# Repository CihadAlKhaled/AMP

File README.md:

# Acceleration Monitor PCB (AMP)

## Background 
The AMP tracks acceleration in the x, y, and z-axis in units of Earth's gravitational acceleration (g). 

## Design
The PCB is powered via a USB connection, which supplies both power and data communication to the computer. An MPU6050 tracks acceleration, which is read by an RP2040 microcontroller over an I²C interface. The computer receives this data and displays it in a console. A 1x2 connector allows the AMP to enter **BOOTSEL** mode when shorted. Additionally, a crystal oscillator provides a stable clock signal for timing operations.

The AMP was designed using KiCad:

### Schematics Design

**Figure 1.0**  

### PCB Design

**Figure 1.1**  

### 3D Rendering of AMP

**Figure 1.2**  

## Hardware
All parts were bought and put together by [JLCPCB](https://jlcpcb.com/). **Table 2.0** has a list of all the components used in the AMP.  

**Table 2.0**  

## Physical PCB
The board arrived, and in **Figure 3.1**, the 1x2 connector is shorted using the red wire, thus in **BOOTSEL** mode.  

### AMP  

**Figure 3.0** 

### BOOTSEL Mode  
  
**Figure 3.1**  

## Software
The software was programmed in MicroPython and uploaded to the RP2040's file system. The software configures the I²C interface by initializing the RP2040's GPIO28 and GPIO29 to the SDA and SCL of the MPU6050. The MPU6050 has a standardized address that the RP2040 communicates with to wake it up and start collecting acceleration data from the AMP.  

### Code uploaded onto the AMP  
  
**Figure 4.0**  

### Output
The code displays the data from the AMP onto the console, showing the x, y, and z components of the acceleration in units of g.  

### Stationary

When the AMP is placed stationary and upright, the z component represents the Earth's gravity on the AMP (~1g = 9.8 m/s²), while x and y are close to zero g. Shown in **Figure 4.1**, there is a slight discrepancy due to the AMP not being perfectly upright, causing Earth's gravity to also appear in the x and y components. Additionally, some noise is present in the readings.  

**Figure 4.1**  

### AMP says WOOF!

The AMP was getting antsy staying stationary, so it went on a walk in the negative y direction while slowly increasing acceleration, as shown in **Figure 4.2**.  

**Figure 4.2**  

### AMP goes up, up, up... and back down?

The AMP being thrown into the air was mimicked (no broken PCB today!). The z-axis shows the acceleration of it going up and then coming back down, as shown in **Figure 4.3**.  

**Figure 4.3**  

### "Around we go"

The AMP was swung around in a circle, and the y-axis represents the measured centripetal acceleration of the PCB, as shown in **Figure 4.4**. The centripetal acceleration could be used to calculate the tension of the wire connecting the computer and the AMP.  

**Figure 4.4**  

## Challenges 
The AMP project was my first PCB design, making it a challenging but valuable learning experience. Understanding how each chip interacted with the others was challenging, and extracting relevant information from datasheets was a struggle in itself. Learning how to **read and interpret datasheets** is a skill I need to continue developing if I want to keep making PCBs.

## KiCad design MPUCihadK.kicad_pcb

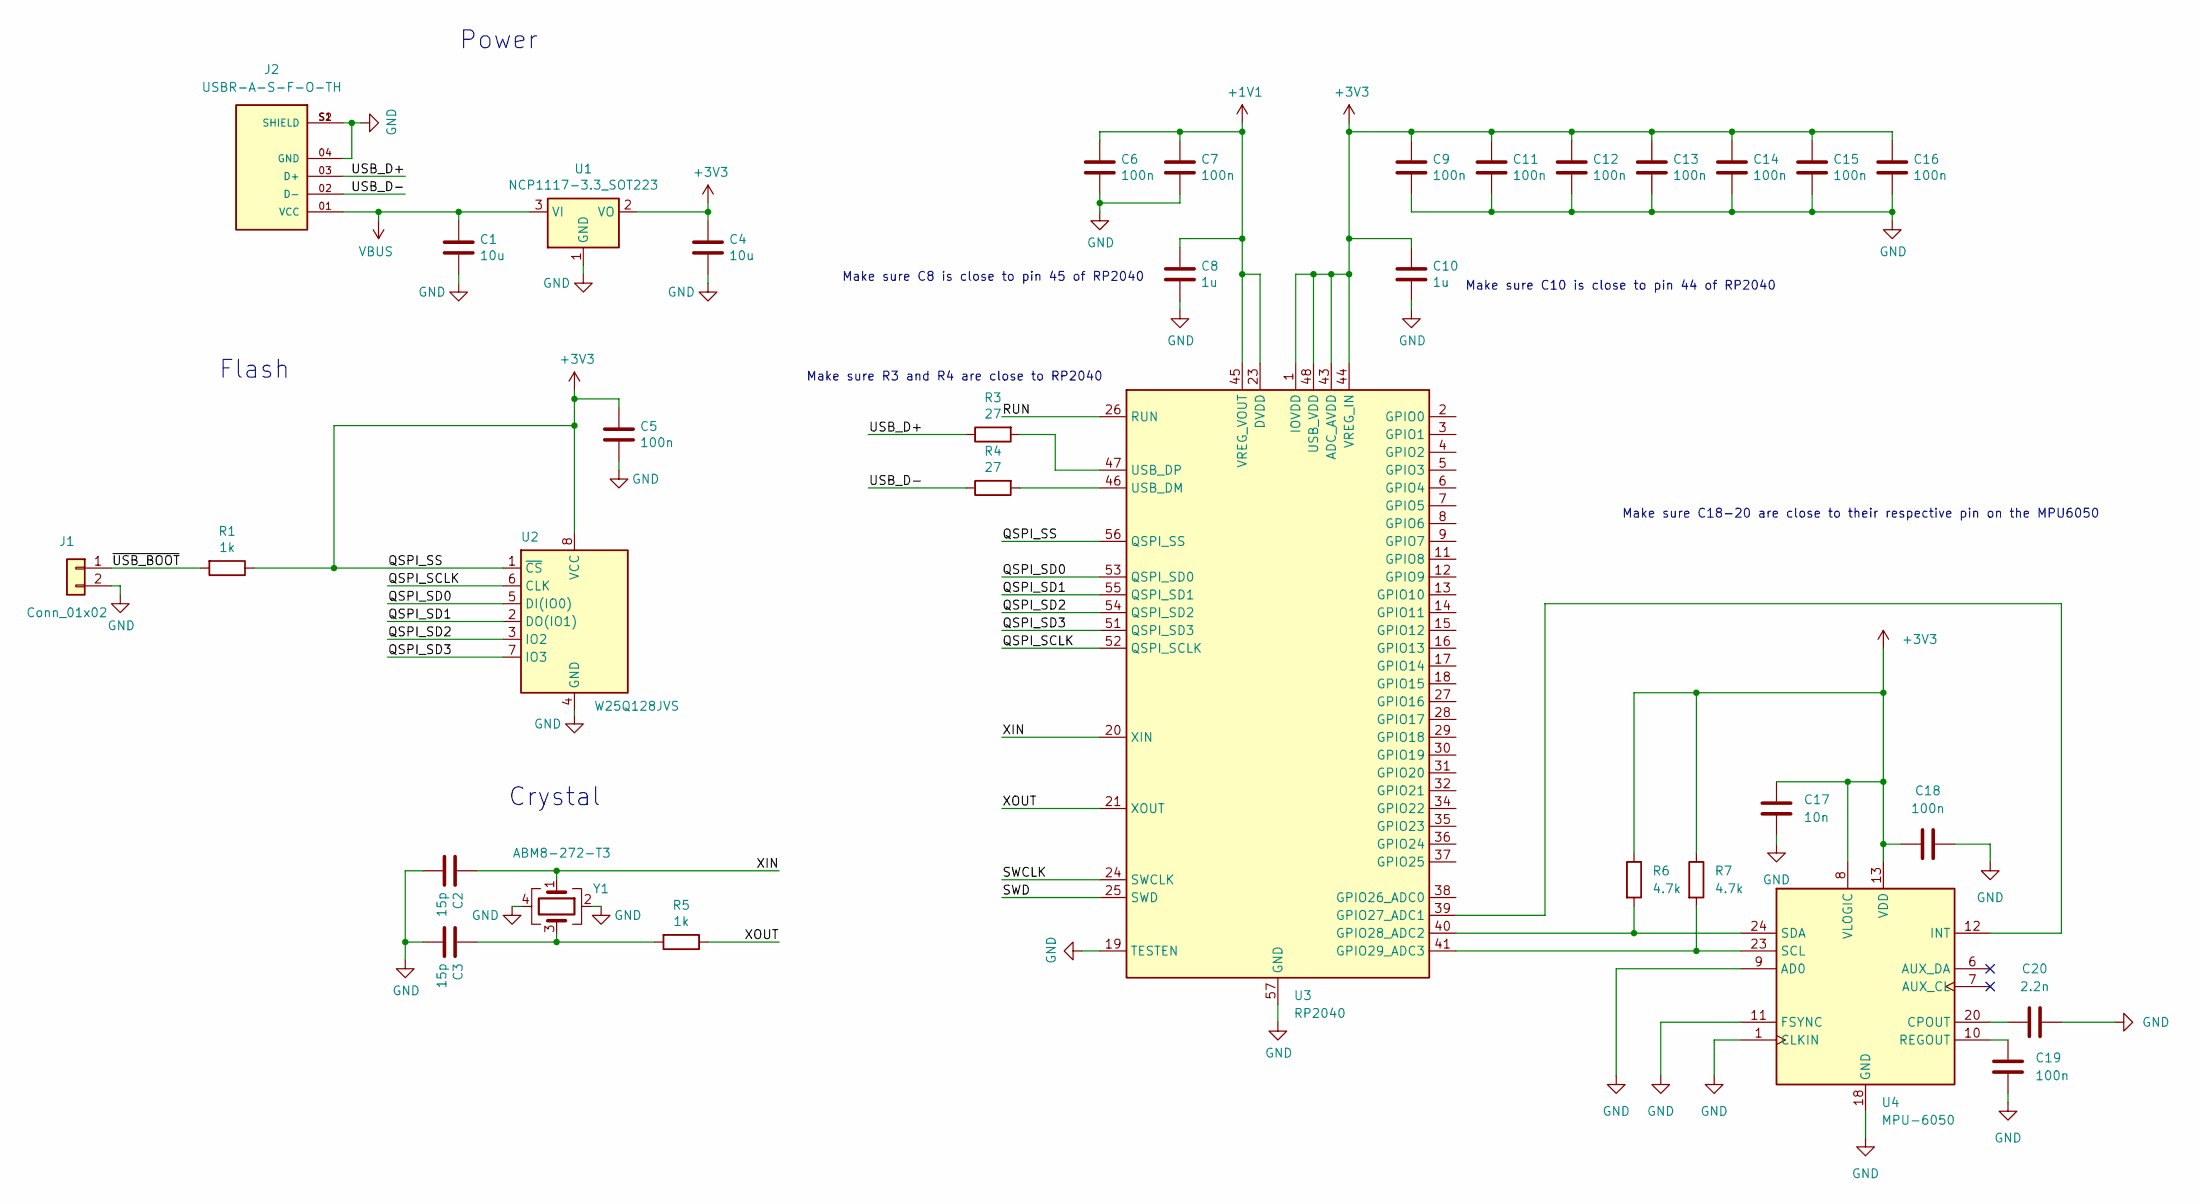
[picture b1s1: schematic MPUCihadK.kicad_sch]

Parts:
C1, C4: 10u; C_0805_2012Metric; LCSC C15525
C2, C3: 15p; C_0402_1005Metric; LCSC C32949
C5, C6, C7, C9, C11, C12, C13, C14, C15, C16, C18, C19: 100n; C_0402_1005Metric; LCSC C1525
C8, C10: 1u; C_0402_1005Metric; LCSC C52923
C17: 10n; C_0402_1005Metric; LCSC C15195
C20: 2.2n; C_0402_1005Metric; LCSC C1531
J1: Conn_01x02; PinHeader_1x02_P2.54mm_Vertical; LCSC C49661
J2: USBR-A-S-F-O-TH; SAMTEC_USBR-A-S-F-O-TH; PARTREV L; LCSC C3197891
R1, R5: 1k; R_0402_1005Metric; LCSC C25543
R3, R4: 27; R_0402_1005Metric; LCSC C25100
R6, R7: 4.7k; R_0402_1005Metric; LCSC C105871
U1: NCP1117-3.3_SOT223; SOT-223-3_TabPin2; LCSC C26537
U2: W25Q128JVS; SOIC-8_5.23x5.23mm_P1.27mm; LCSC C2613930
U3: RP2040; QFN-56-1EP_7x7mm_P0.4mm_EP3.2x3.2mm; LCSC C2040
U4: MPU-6050; InvenSense_QFN-24_4x4mm_P0.5mm; LCSC C24112
Y1: ABM8-272-T3; Crystal_SMD_3225-4Pin_3.2x2.5mm; LCSC C20625731

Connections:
+1V1: C6.1, C7.1, C8.1, U3.23 (DVDD), U3.45 (VREG_VOUT), U3.50 (DVDD)
/QSPI_SCLK: U2.6 (CLK), U3.52 (QSPI_SCLK)
/QSPI_SD0: U2.5 (DI(IO0)), U3.53 (QSPI_SD0)
/QSPI_SD1: U2.2 (DO(IO1)), U3.55 (QSPI_SD1)
/QSPI_SD2: U2.3 (IO2), U3.54 (QSPI_SD2)
/QSPI_SD3: U2.7 (IO3), U3.51 (QSPI_SD3)
/RUN: U3.26 (RUN)
/SWCLK: U3.24 (SWCLK)
/SWD: U3.25 (SWD)
/USB_D+: J2.03 (D+), R3.1
/USB_D-: J2.02 (D-), R4.1
/XIN: C2.1, U3.20 (XIN), Y1.1
/XOUT: R5.1, U3.21 (XOUT)
/~USB_BOOT: J1.1, R1.2
GND: C1.2, C2.2, C3.2, C4.2, C5.2, C6.2, C7.2, C8.2, C9.2, C10.2, C11.2, C12.2, C13.2, C14.2, C15.2, C16.2, C17.2, C18.2, C19.2, C20.2, J1.2, J2.04 (GND), J2.S1 (SHIELD), J2.S2 (SHIELD), U1.1 (GND), U2.4 (GND), U3.19 (TESTEN), U3.57 (GND), U4.1 (CLKIN), U4.9 (AD0), U4.11 (FSYNC), U4.18 (GND), Y1.2, Y1.4
unnamed: C3.1, R5.2, Y1.3
unnamed: U3.39 (GPIO27_ADC1), U4.12 (INT)
unnamed: R6.2, U3.40 (GPIO28_ADC2), U4.24 (SDA)
unnamed: R7.2, U3.41 (GPIO29_ADC3), U4.23 (SCL)
unnamed: R4.2, U3.46 (USB_DM)
unnamed: R3.2, U3.47 (USB_DP)
unnamed: C20.1, U4.20 (CPOUT)
unnamed: C19.1, U4.10 (REGOUT)
VBUS: C1.1, J2.01 (VCC), U1.3 (VI)

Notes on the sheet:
Make sure C8 is close to pin 45 of RP2040
Make sure C10 is close to pin 44 of RP2040
Make sure C18-20 are close to their respective pin on the MPU6050
Make sure R3 and R4 are close to RP2040
Crystal
Power
Flash

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
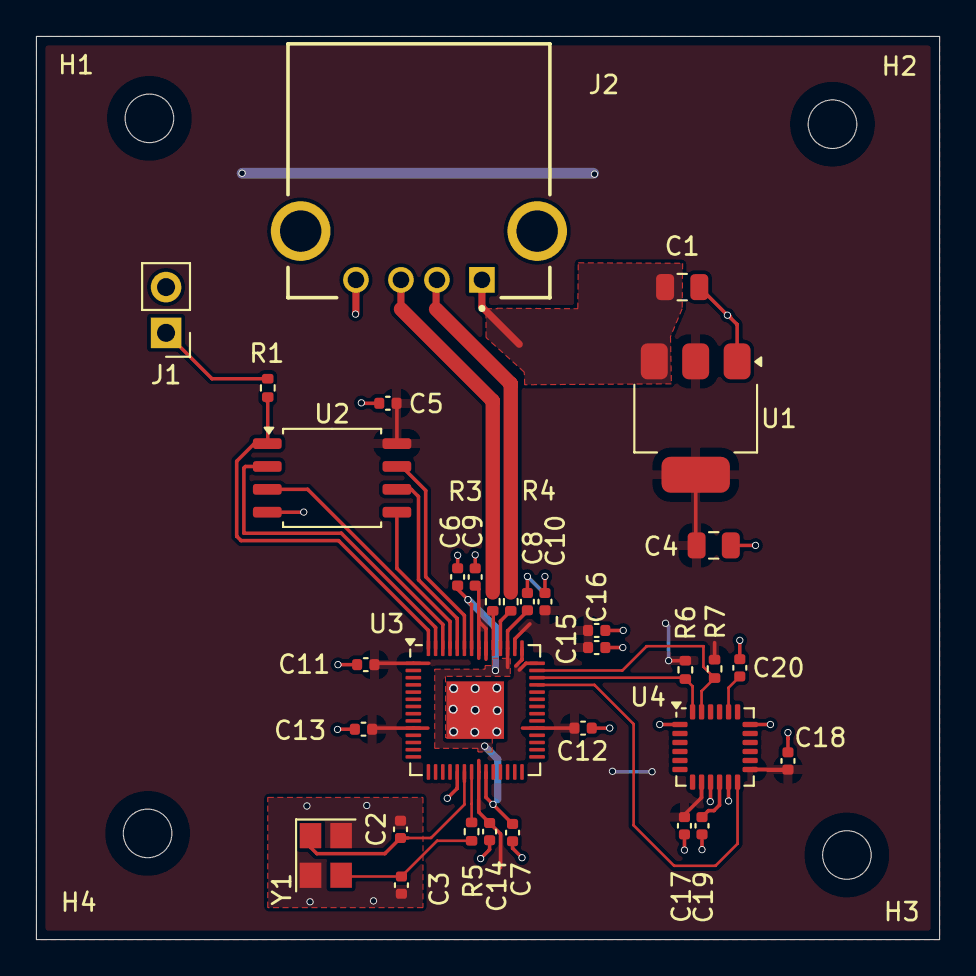
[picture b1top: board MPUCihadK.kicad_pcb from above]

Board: 2 copper layers, 50.2 x 50.2 mm, 37 parts (0 on the bottom side), 23 nets.

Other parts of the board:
H1, H2, H3, H4: MountingHole; MountingHole_2.7mm_M2.5

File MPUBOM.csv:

"Reference","Value","Datasheet","Footprint","Qty","DNP","LCSC","Link"
"C1,C4","10u","https://www.lcsc.com/datasheet/lcsc_datasheet_2208231630_Sam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","Capacitor_SMD:C_0805_2012Metric","2","","C15525","https://jlcpcb.com/partdetail/C15525"
"C2,C3","15p","https://www.lcsc.com/datasheet/lcsc_datasheet_2304140030_Sam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","Capacitor_SMD:C_0402_1005Metric","2","","C32949","https://jlcpcb.com/partdetail/C32949"
"C5,C6,C7,C9,C11,C12,C13,C14,C15,C16,C18,C19","100n","https://www.lcsc.com/datasheet/lcsc_datasheet_2304140030_Sam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","Capacitor_SMD:C_0402_1005Metric","12","","C1525","https://jlcpcb.com/partdetail/C1525"
"C8,C10","1u","https://www.lcsc.com/datasheet/lcsc_datasheet_2304140030_Sam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","Capacitor_SMD:C_0402_1005Metric","2","","C52923","https://jlcpcb.com/partdetail/C52923"
"C17","10n","https://www.lcsc.com/datasheet/lcsc_datasheet_2304140030_Sam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","Capacitor_SMD:C_0402_1005Metric","1","","C15195","https://jlcpcb.com/partdetail/15869-CL05B103KB5NNNC/C15195"
"C20","2.2n","https://www.lcsc.com/datasheet/lcsc_datasheet_2304140030_FH-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","Capacitor_SMD:C_0402_1005Metric","1","","C1531","https://jlcpcb.com/partdetail/1883-0402B222K500NT/C1531"
"J1","Conn_01x02","https://www.lcsc.com/datasheet/lcsc_datasheet_2304140030_BOO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","Connector_PinHeader_2.54mm:PinHeader_1x02_P2.54mm_Vertical","1","","C49661","https://jlcpcb.com/partdetail/50669-2_54_1_2P/C49661"
"J2","USBR-A-S-F-O-TH","https://wmsc.lcsc.com/wmsc/upload/file/pdf/v2/lcsc/240129133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","USBR-A-S-F-O-TH (1):SAMTEC_USBR-A-S-F-O-TH","1","","C3197891","https://jlcpcb.com/partdetail/Samtec-USBR_A_S_F_OTH/C3197891"
"R1,R5","1k","https://www.lcsc.com/datasheet/lcsc_datasheet_2205311845_UNI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","Resistor_SMD:R_0402_1005Metric","2","","C25543","https://jlcpcb.com/partdetail/26286-0402WGJ0102TCE/C25543"
"R3,R4","27","https://www.lcsc.com/datasheet/lcsc_datasheet_2205311900_UNI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","Resistor_SMD:R_0402_1005Metric","2","","C25100","https://jlcpcb.com/partdetail/25843-0402WGF270JTCE/C25100"
"R6,R7","4.7k","https://www.lcsc.com/datasheet/lcsc_datasheet_2304140030_YAG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","Resistor_SMD:R_0402_1005Metric","2","","C105871","https://jlcpcb.com/parts/componentSearch?searchTxt=4.7k%200402"
"U1","NCP1117-3.3_SOT223","http://www.onsemi.com/pub_link/Collateral/NCP1117-D.PDF","Package_TO_SOT_SMD:SOT-223-3_TabPin2","1","","C26537","https://jlcpcb.com/partdetail/Onsemi-NCP1117ST33T3G/C26537"
"U2","W25Q128JVS","http://www.winbond.com/resource-files/w25q128jv_dtr%20revc%2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","Package_SO:SOIC-8_5.23x5.23mm_P1.27mm","1","","C2613930","https://jlcpcb.com/partdetail/WinbondElec-W25Q128JVSIM/C2613930"
"U3","RP2040","https://datasheets.raspberrypi.com/rp2040/rp2040-datasheet.pdf","Package_DFN_QFN:QFN-56-1EP_7x7mm_P0.4mm_EP3.2x3.2mm","1","","C2040","https://jlcpcb.com/partdetail/RaspberryPi-RP2040/C2040"
"U4","MPU-6050","https://invensense.tdk.com/wp-content/uploads/2015/02/MPU-60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","Sensor_Motion:InvenSense_QFN-24_4x4mm_P0.5mm","1","","C24112","https://jlcpcb.com/partdetail/TdkInvensense-MPU6050/C24112"
"Y1","ABM8-272-T3","https://jlcpcb.com/api/file/downloadByFileSystemAccessId/855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","Crystal:Crystal_SMD_3225-4Pin_3.2x2.5mm","1","","C20625731 ","https://jlcpcb.com/partdetail/AbraconLlc-ABM8_272T3/C20625731"
